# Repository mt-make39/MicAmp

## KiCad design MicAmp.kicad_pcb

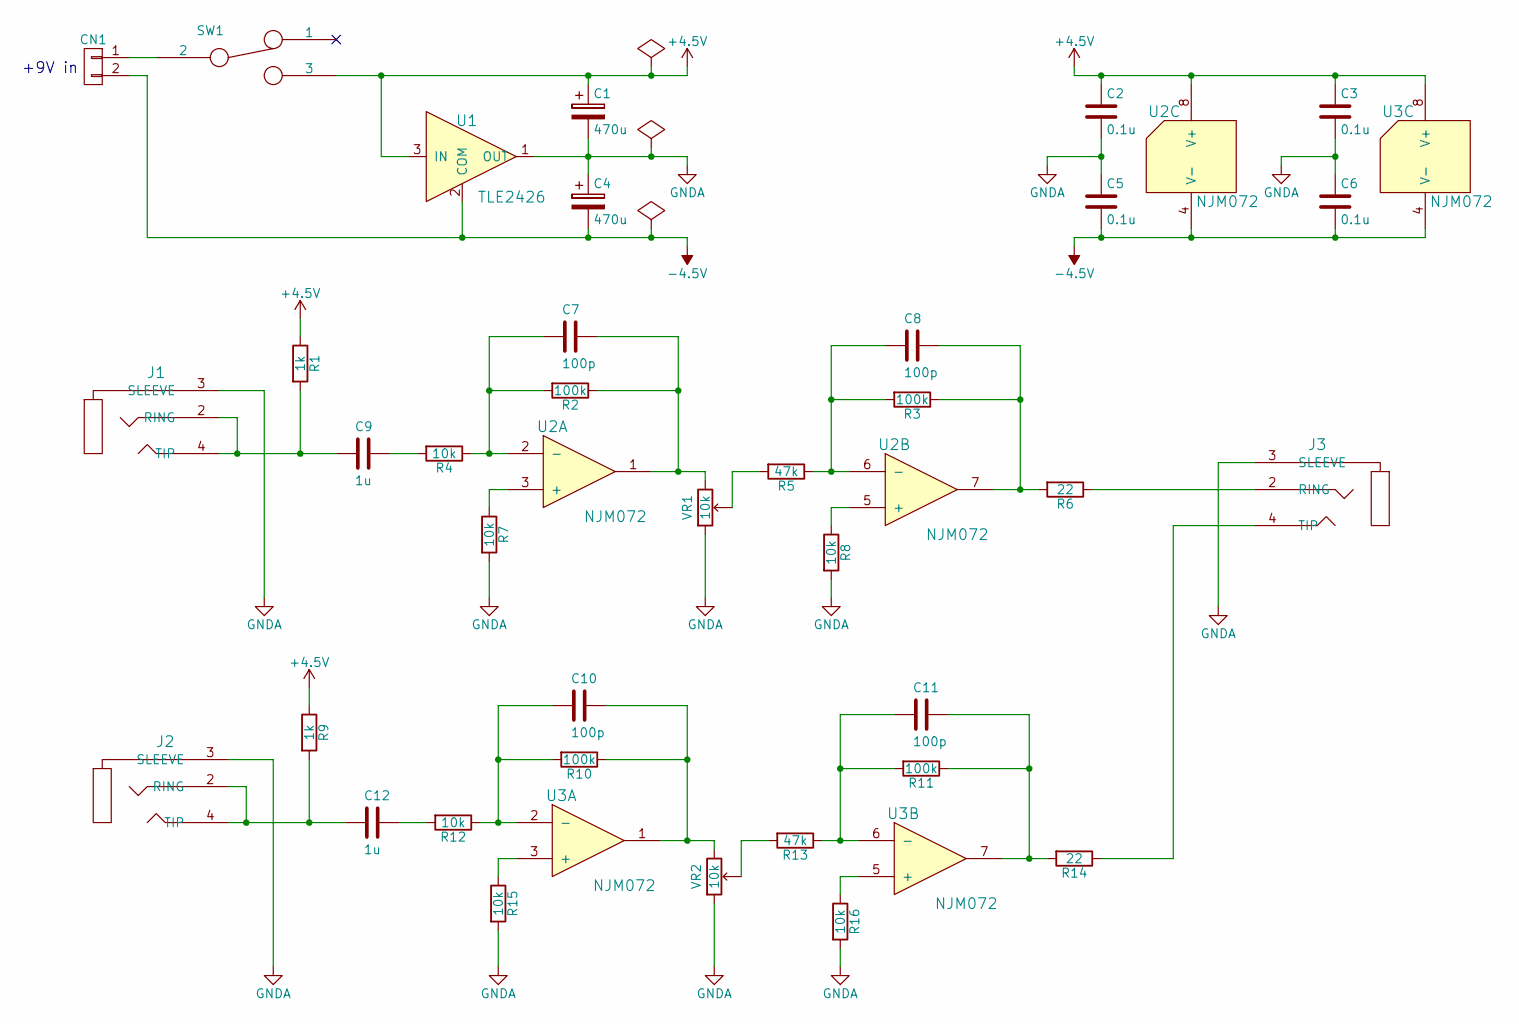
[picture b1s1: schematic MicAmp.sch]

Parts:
C1, C4: 470u; C_Φ8_35
C2, C3, C5, C6: 0.1u; C_1608
C7, C8, C10, C11: 100p; C_1608
C9, C12: 1u; C_1608
CN1: CONN_01X02; XH_2P
J1, J2, J3: 3.5mm_stereo_mini_ST_005_G; STEREO_MINI_35
R1, R9: 1k; R_1608
R2, R3, R10, R11: 100k; R_1608
R4, R7, R8, R12, R15, R16: 10k; R_1608
R5, R13: 47k; R_1608
R6, R14: 22; R_1608
SW1: SWITCH_INV; SK-12D01
U1: TLE2426; TO_92_254
U2, U3: NJM072; DIP_8pin
VR1, VR2: 10k; VR_3362P

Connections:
+4.5V: C1.1, C2.1, C3.1, R1.1, R9.1, SW1.3, U1.3 (IN), U2.8 (V+), U3.8 (V+)
-4.5V: C4.2, C5.2, C6.2, CN1.2, U1.2 (COM), U2.4 (V-), U3.4 (V-)
GNDA: C1.2, C2.2, C3.2, C4.1, C5.1, C6.1, J1.3 (SLEEVE), J2.3 (SLEEVE), J3.3 (SLEEVE), R7.2, R8.2, R15.2, R16.2, U1.1 (OUT), VR1.3, VR2.3
unnamed: C7.1, R2.1, U2.1, VR1.1
unnamed: C7.2, R2.2, R4.1, U2.2 (-)
unnamed: C8.1, R3.1, R6.2, U2.7
unnamed: C8.2, R3.2, R5.1, U2.6 (-)
unnamed: C9.1, R4.2
unnamed: C9.2, J1.2 (RING), J1.4 (TIP), R1.2
unnamed: C10.1, R10.1, U3.1, VR2.1
unnamed: C10.2, R10.2, R12.1, U3.2 (-)
unnamed: C11.1, R11.1, R14.2, U3.7
unnamed: C11.2, R11.2, R13.1, U3.6 (-)
unnamed: C12.1, R12.2
unnamed: C12.2, J2.2 (RING), J2.4 (TIP), R9.2
unnamed: CN1.1, SW1.2
unnamed: J3.2 (RING), R6.1
unnamed: J3.4 (TIP), R14.1
unnamed: R5.2, VR1.2
unnamed: R7.1, U2.3 (+)
unnamed: R8.1, U2.5 (+)
unnamed: R13.2, VR2.2
unnamed: R15.1, U3.3 (+)
unnamed: R16.1, U3.5 (+)

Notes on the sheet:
+9V in

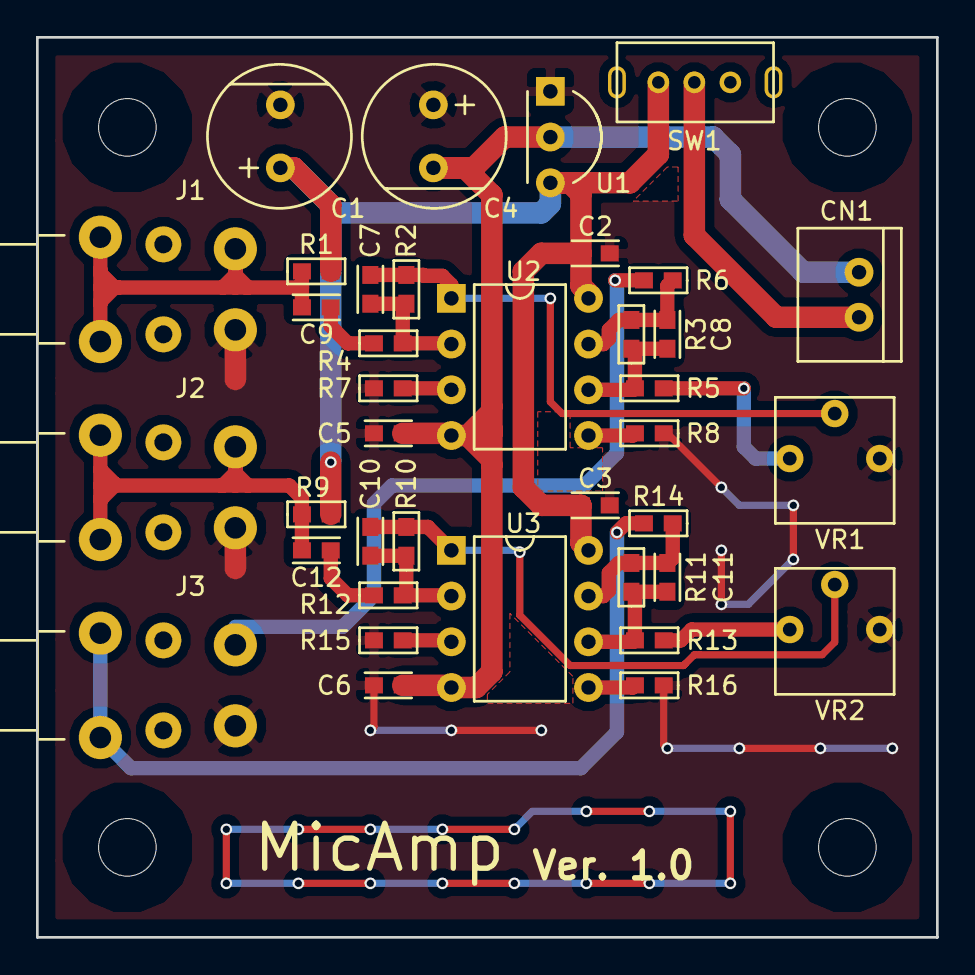
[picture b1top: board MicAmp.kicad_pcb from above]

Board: 2 copper layers, 50.0 x 50.0 mm, 38 parts (0 on the bottom side), 24 nets.

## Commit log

2019-01-29 Add new
2019-01-29 add file
2019-01-29 test3
